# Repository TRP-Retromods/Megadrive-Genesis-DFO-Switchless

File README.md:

# Megadrive-Genesis-DFO-Switchless
This is a twist on classic DFO from Micro where I put a PIC16F630 and the back for the switchless mod. You need D4S code.

# Links for the Programmer and classic DFO:
https://nfggames.com/forum2/index.php?topic=5744.0
https://oshpark.com/profiles/micro

https://circuit-board.de/forum/index.php/Thread/7810-Sega-32X-Switchless-Mod-f%C3%BCr-Mega-Drive-1-und-auch-2/?s=005d89b5fd35d5ff06d198493b633b89d1ca043f

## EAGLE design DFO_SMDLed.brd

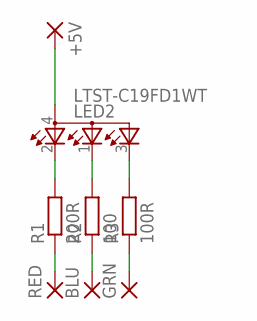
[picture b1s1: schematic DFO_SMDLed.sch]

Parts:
+5V: SMD2TOP; SMD_SOIC
BLU: SMD2TOP; SMD_SOIC
GRN: SMD2TOP; SMD_SOIC
LED2: LTST-C19FD1WT
R1: 200R; R0805
R2: 100; R0805
R3: 100R; R0805
RED: SMD2TOP; SMD_SOIC

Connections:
unnamed: +5V.1, LED2.4 (A)
unnamed: LED2.2 (CRED), R1.2
unnamed: LED2.1 (CBLUE), R2.2
unnamed: LED2.3 (CGREEN), R3.2
unnamed: R1.1, RED.1
unnamed: BLU.1, R2.1
unnamed: GRN.1, R3.1

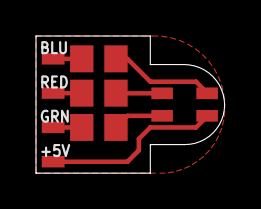
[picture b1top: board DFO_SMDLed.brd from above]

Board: 2 copper layers, 10.5 x 7.6 mm, 8 parts (0 on the bottom side), 7 nets.

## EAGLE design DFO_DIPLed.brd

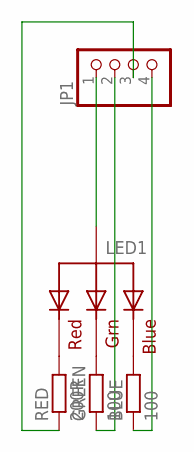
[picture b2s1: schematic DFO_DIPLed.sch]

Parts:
BLUE: 100; R0805
GREEN: 100; R0805
JP1: PINHD-1X04_2.00; 1X04M
LED1: RGBLED_CA-5MM; LED5MMRGB
RED: 200R; R0805

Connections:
unnamed: LED1.1 (RED), RED.2
unnamed: GREEN.2, LED1.3 (GREEN)
unnamed: BLUE.2, LED1.4 (BLUE)
unnamed: JP1.3, RED.1
unnamed: JP1.1, LED1.2 (VCC)
unnamed: GREEN.1, JP1.2
unnamed: BLUE.1, JP1.4

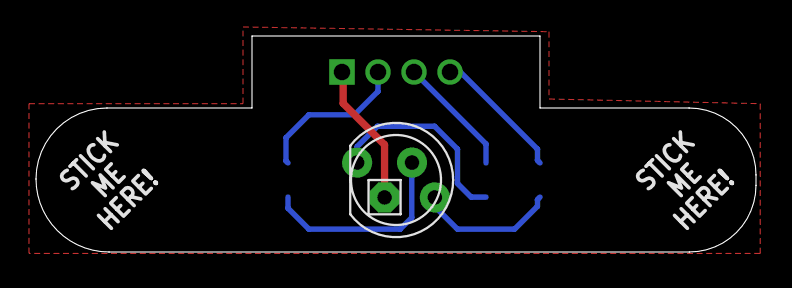
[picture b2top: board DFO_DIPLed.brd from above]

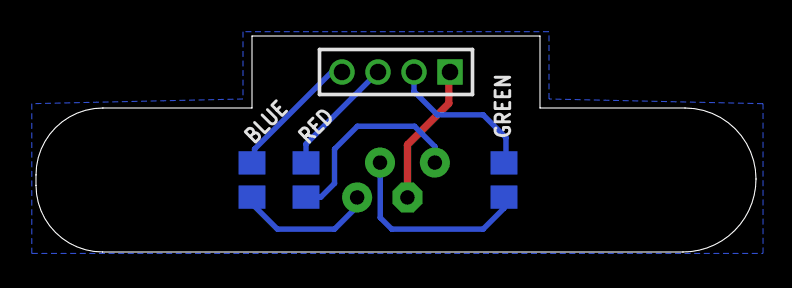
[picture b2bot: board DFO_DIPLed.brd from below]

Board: 2 copper layers, 40.0 x 12.0 mm, 5 parts (4 on the bottom side), 7 nets.

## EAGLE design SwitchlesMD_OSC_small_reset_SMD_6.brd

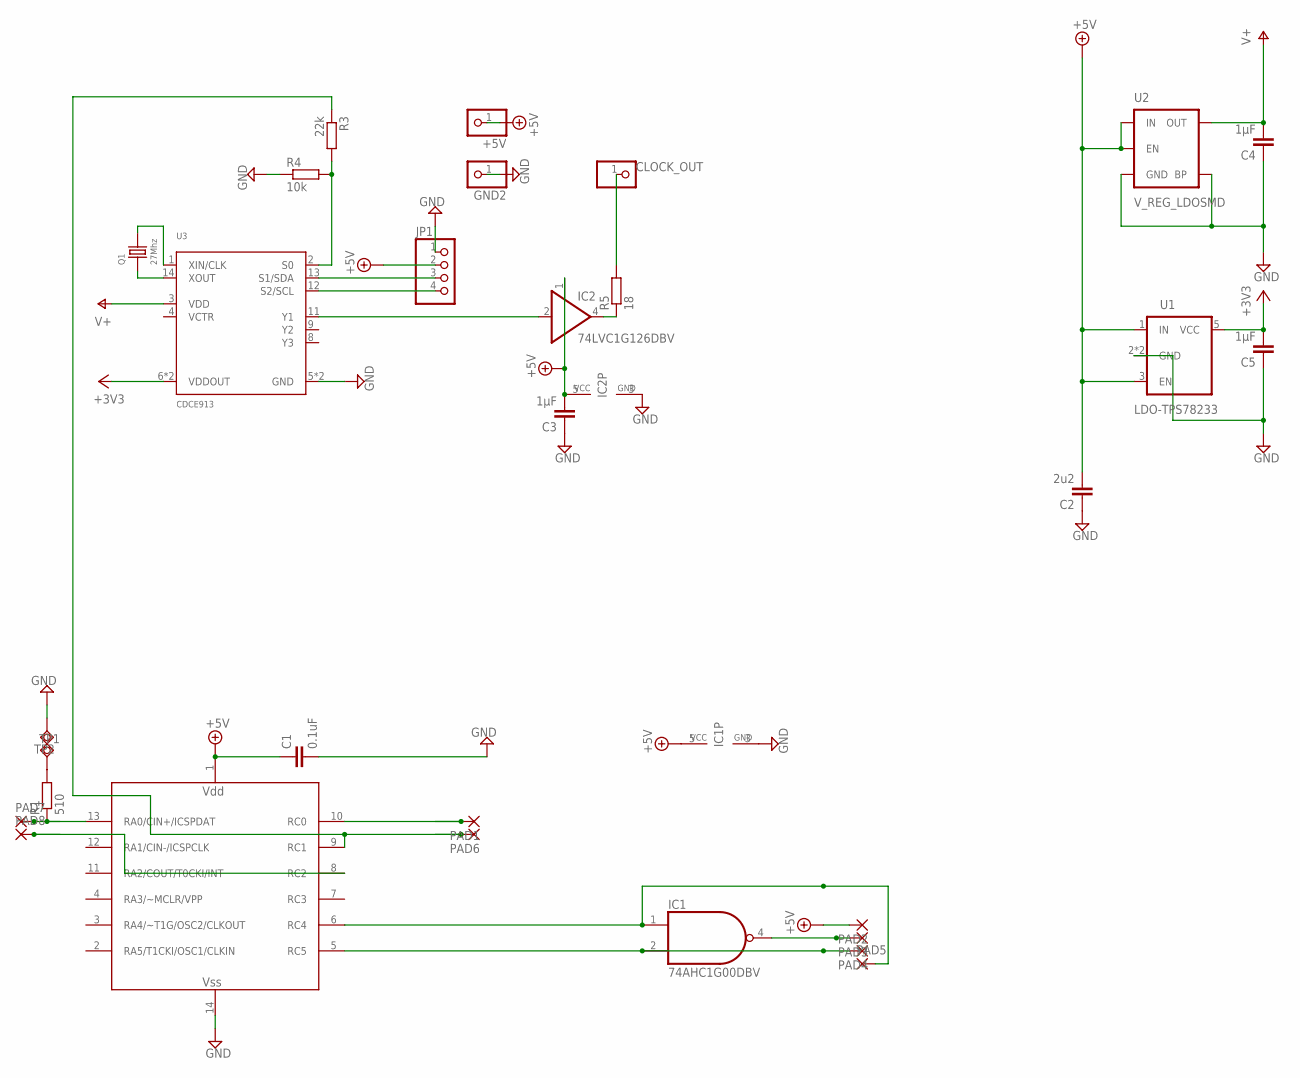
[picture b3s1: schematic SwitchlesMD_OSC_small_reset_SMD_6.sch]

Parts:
+5V: PINHD-1X01_2.54; 1X01
C1: 0.1uF; C0603
C2: 2u2; C0603
C3, C4, C5: 1µF; C0603
CLOCK_OUT: PINHD-1X01_2.54; 1X01
GND2: PINHD-1X01_2.54; 1X01
IC1: 74AHC1G00DBV; SOT23-5
IC2: 74LVC1G126DBV; SOT23-5
JP1: PINHD-1X04_2.00; 1X04M
PAD1, PAD2, PAD3, PAD4, PAD5, PAD6, PAD7, PAD8: SMD2TOP; SMD_SOIC
PIC16F630: PIC16F630SL; SOIC-14
Q1: 27Mhz; X2-SMD-5.0X3.2X1.3MM
R1: 510; R0603
R3: 22k; R0603
R4: 10k; R0603
R5: 18; R0603
TP1, TP2: TPSQTP07SQ; TP07SQ
U1: LDO-TPS78233; SOT23-5
U2: V_REG_LDOSMD; SOT23-5
U3: CDCE913; TSSOP14

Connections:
+1V8: C4.2, U2.5 (OUT), U3.3 (VDD)
+3V3: C5.2, U1.5 (VCC), U3.6 (VDDOUT), U3.7 (VDDOUT)
+5V: +5V.1, C1.1, C2.2, C3.2, IC1.5 (VCC), IC2.1 (OE), IC2.5 (VCC), JP1.2, PAD2.1, PIC16F630.1 (VDD), U1.1 (IN), U1.3 (EN), U2.1 (IN), U2.3 (EN)
GND: C1.2, C2.1, C3.1, C4.1, C5.1, GND2.1, IC1.3 (GND), IC2.3 (GND), JP1.1, PIC16F630.14 (VSS), R4.1, TP2.TP, U1.2 (GND), U1.4 (GND), U2.2 (GND), U2.4 (BP), U3.5 (GND), U3.10 (GND)
LANG: PAD1.1, PIC16F630.10 (RC0)
LED_EU: IC1.2 (I1), PAD4.1, PIC16F630.5 (RC5)
LED_JP: IC1.1 (I0), PAD5.1, PIC16F630.6 (RC4)
LED_US: IC1.4 (O), PAD3.1
unnamed: R1.2, TP1.TP
unnamed: PAD8.1, PIC16F630.8 (RC2)
unnamed: PAD7.1, PIC16F630.13 (RA0/CIN+/ICSPDAT), R1.1
unnamed: R3.2, R4.2, U3.2 (S0)
unnamed: IC2.4 (O), R5.1
unnamed: CLOCK_OUT.1, R5.2
unnamed: Q1.1, U3.14 (XOUT)
unnamed: Q1.2, U3.1 (XIN/CLK)
unnamed: JP1.3, U3.13 (S1/SDA)
unnamed: JP1.4, U3.12 (S2/SCL)
unnamed: IC2.2 (I), U3.11 (Y1)
VIDEO: PAD6.1, PIC16F630.9 (RC1), R3.1

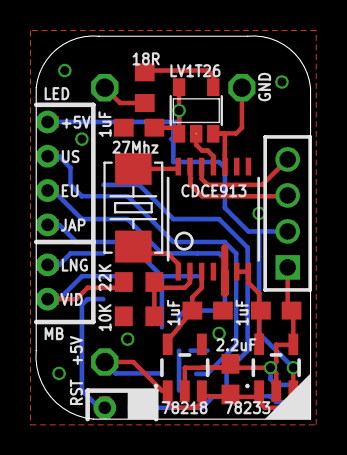
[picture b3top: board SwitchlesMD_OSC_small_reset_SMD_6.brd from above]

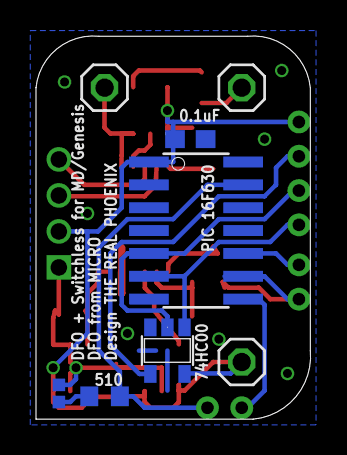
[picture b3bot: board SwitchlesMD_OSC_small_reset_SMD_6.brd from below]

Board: 2 copper layers, 15.3 x 21.3 mm, 30 parts (9 on the bottom side), 20 nets.

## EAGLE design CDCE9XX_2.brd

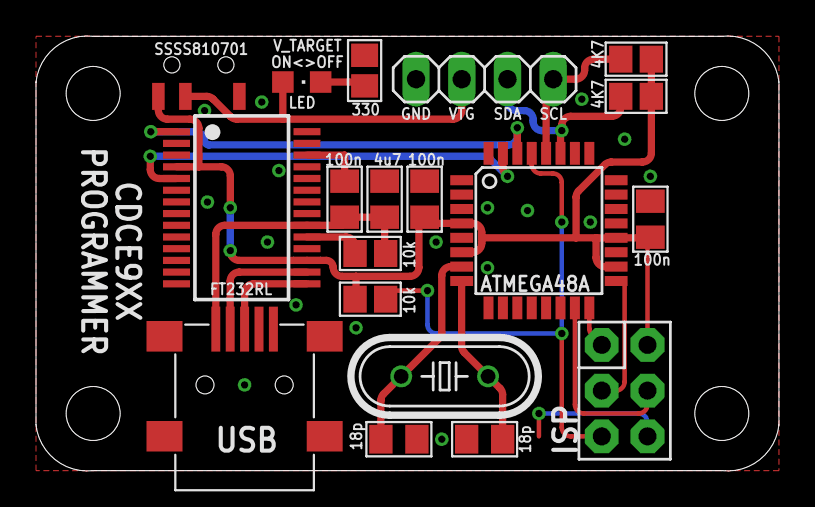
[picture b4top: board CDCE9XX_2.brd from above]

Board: 2 copper layers, 41.3 x 24.2 mm, 19 parts (0 on the bottom side), 18 nets.

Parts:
C1, C5, C6: 100n; C0805K_B
C2: 4u7; C0805K_B
C3, C4: 18p; C0805K_B
IC1: FT232RL; SSOP28
IC2: ATMEGA48A; TQFP32-08
JP1: 1X04
LED: CHIPLED_0805
Q1: 10M; HC49/S
R1, R2: 10k; R0805_B
R3, R4: 4K7; R0805_B
R5: 330; R0805_B
U$2: ISPBIG_POGO_PINS; 2X3_ISP_BIGPOGO
U$3: TOGGLE_SWITCH; SSSS810701
USB1: LUMBERG2486_01_MINI_USB_B; LUM2486-01

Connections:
!RESET: IC2.29, R1.2, U$2.RESET
+3V3: C5.2, C6.2, IC1.4, IC1.17, IC2.4, IC2.6, IC2.18, IC2.20, R1.1, R3.2, R4.2, U$2.VCC, U$3.T3
FT_RX: IC1.5, IC2.31
FT_TX: IC1.1, IC2.30
GND: C1.1, C2.1, C3.1, C4.1, C5.1, C6.1, IC1.7, IC1.18, IC1.21, IC1.25, IC1.26, IC2.3, IC2.5, IC2.21, JP1.1, R5.2, U$2.GND, USB1.5GND
unnamed: LED.C, R5.1
unnamed: C1.2, C2.2, IC1.20, R2.2, USB1.1VBUS
unnamed: IC1.19, R2.1
unnamed: C3.2, IC2.7, Q1.2
unnamed: C4.2, IC2.8, Q1.1
unnamed: IC2.16, U$2.MISO
unnamed: IC2.17, U$2.SCK
unnamed: IC2.15, U$2.MOSI
SCL: IC2.28, JP1.4, R4.1
SDA: IC2.27, JP1.3, R3.1
USB+: IC1.15, USB1.3D+
USB-: IC1.16, USB1.2D-
V_TARGET: JP1.2, LED.A, U$3.T2

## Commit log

2018-12-27 Add files via upload
    Add Eagle board, and TXT file for Multibios Order.
2018-12-27 Add files via upload
    add HEX file for PIC. This is D4S's code.
2019-05-11 Add LEDs PCB
    Add LEDs PCB:
    - DIP for MegaDrive/Genesis Model 1
    - SMD for Model 2
2019-05-11 adding CDCE9XX PCB
    adding CDCE9XX PCB - Eagle and Gerber file
2019-05-11 Addind Gerber File for DFO switchless
2020-12-10 Cleaned and organized deposit.
    - Cleaned and organized deposit.
    - Add Firmware/Software for DFO Programmer
    - Add Megadrive/Genesis2 frequency for DFO
2021-04-12 Create LICENSE
2023-05-16 Add original DS4 pdf installation guide

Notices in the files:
parts and their libraries:
SparkFun-PowerIC: Licensing: Creative Commons ShareAlike 4.0 International - https://creativecommons.org/licenses/by-sa/4.0
